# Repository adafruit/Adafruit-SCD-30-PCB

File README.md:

## Adafruit SCD-30 NDIR CO2 Temperature and Humidity Sensor PCB

<a href="http://www.adafruit.com/products/4867"><br/>
Click here to purchase one from the Adafruit shop</a>

PCB files for the Adafruit SCD-30 NDIR CO2 Temperature and Humidity Sensor. 

Format is EagleCAD schematic and board layout
* https://www.adafruit.com/product/4867

### Description

INSERT PRODUCT COPY HERE

### License

Adafruit invests time and resources providing this open source design, please support Adafruit and open-source hardware by purchasing products from [Adafruit](https://www.adafruit.com)!

Designed by Limor Fried/Ladyada for Adafruit Industries.

Creative Commons Attribution/Share-Alike, all text above must be included in any redistribution. 
See license.txt for additional details.

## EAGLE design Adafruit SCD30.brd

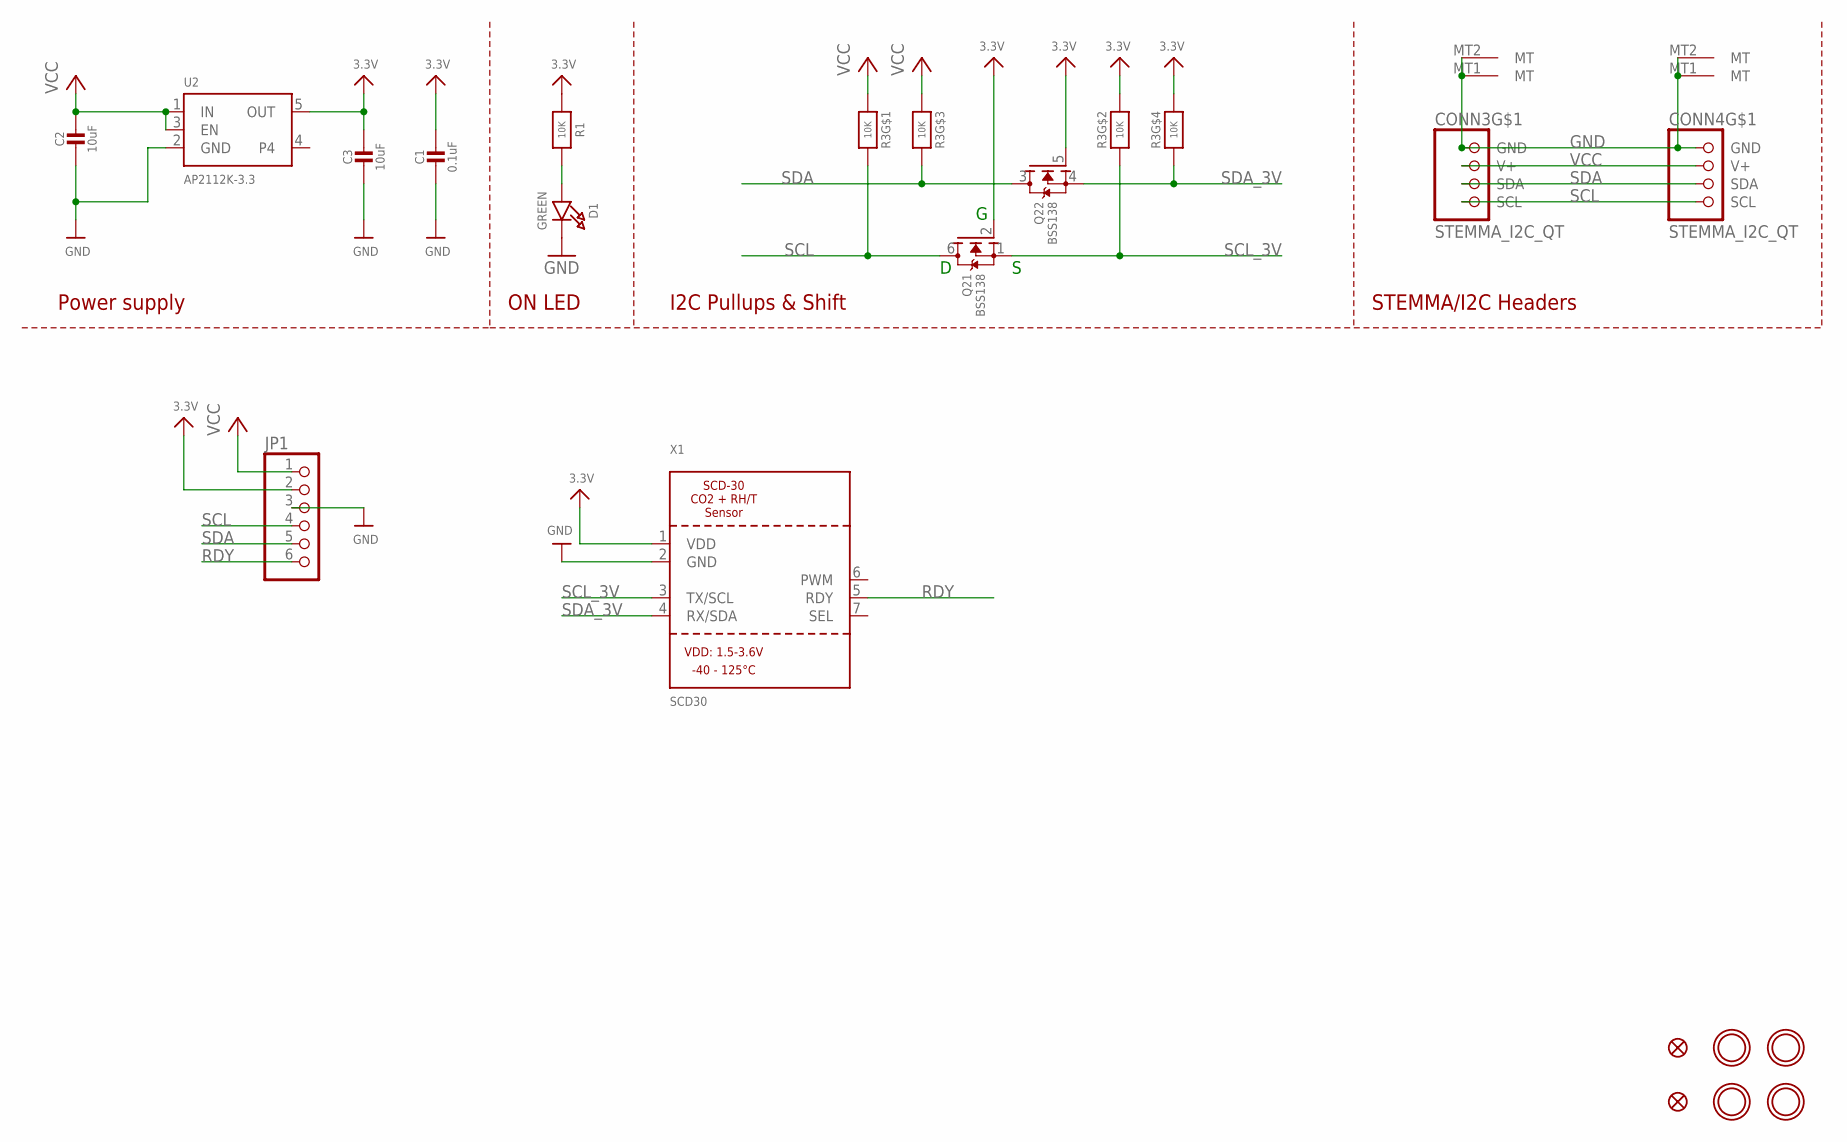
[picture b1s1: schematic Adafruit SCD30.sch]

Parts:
C1: 0.1uF; 0603-NO
C2, C3: 10uF; 0805-NO
CONN3, CONN4: STEMMA_I2C_QT; JST_SH4
D1: GREEN; CHIPLED_0603_NOOUTLINE
FID3, FID4: FIDUCIAL_1MM
JP1: HEADER-1X670MIL; 1X06_ROUND_70
Q2: BSS138; SOT363
R1: 10K; 0603-NO
R3: 10K; RESPACK_4X0603
U2: AP2112K-3.3; SOT23-5
U$1, U$17, U$19, U$21: MOUNTINGHOLE2.5; MOUNTINGHOLE_2.5_PLATED
X1: SCD30

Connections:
3.3V: C1.1, C3.1, JP1.2, Q2.2 (G), Q2.5 (G), R1.1, R3.2 (1), R3.4 (1), U2.5 (OUT), X1.1 (VDD)
GND: C1.2, C2.2, C3.2, CONN3.1 (GND), CONN3.MT1 (MT), CONN3.MT2 (MT), CONN4.1 (GND), CONN4.MT1 (MT), CONN4.MT2 (MT), D1.C, JP1.3, U2.2 (GND), X1.2 (GND)
unnamed: D1.A, R1.2
RDY: JP1.6, X1.5 (RDY)
SCL: CONN3.4 (SCL), CONN4.4 (SCL), JP1.4, Q2.6 (D), R3.8 (2)
SCL_3V: Q2.1 (S), R3.7 (2), X1.3 (TX/SCL)
SDA: CONN3.3 (SDA), CONN4.3 (SDA), JP1.5, Q2.3 (D), R3.6 (2)
SDA_3V: Q2.4 (S), R3.5 (2), X1.4 (RX/SDA)
VCC: C2.1, CONN3.2 (V+), CONN4.2 (V+), JP1.1, R3.1, R3.3 (1), U2.1 (IN), U2.3 (EN)

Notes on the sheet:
I2C Pullups & Shift
STEMMA/I2C Headers
ON LED
Power supply

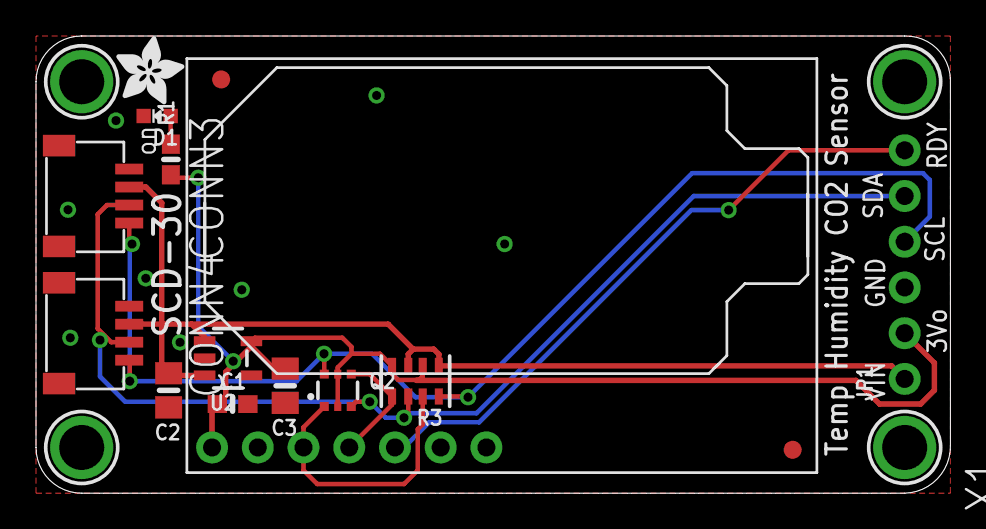
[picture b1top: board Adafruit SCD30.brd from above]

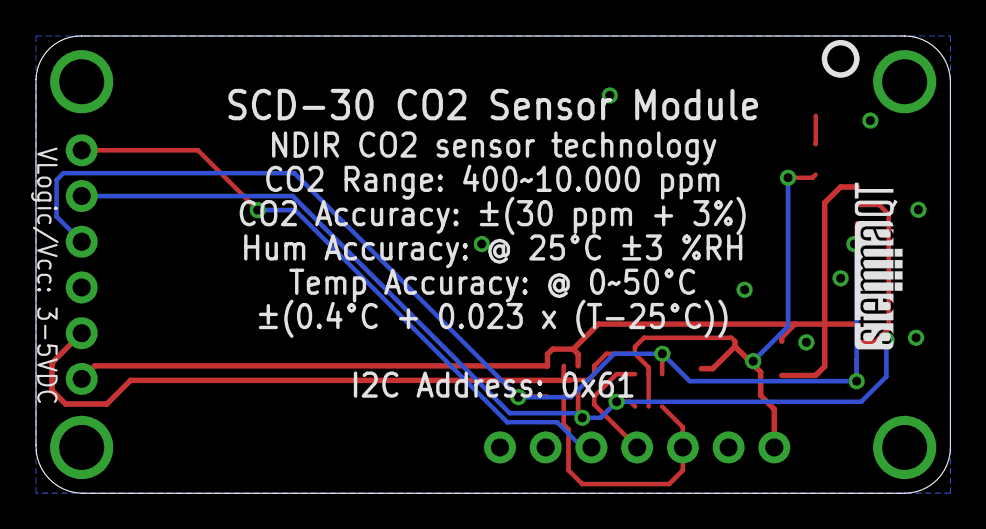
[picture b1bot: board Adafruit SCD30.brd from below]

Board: 2 copper layers, 50.8 x 25.4 mm, 21 parts (2 on the bottom side), 9 nets.

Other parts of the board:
U$22: ADAFRUIT_3.5MM
U$25: PCBFEAT-REV-040
U$30: STEMMAQT

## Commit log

2021-01-05 Adding board files.
2021-01-06 Add asset image.

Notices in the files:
parts and their libraries:
microbuilder: This work is placed in the public domain, and may be freely used for commercial and non-commercial work with the following conditions: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
